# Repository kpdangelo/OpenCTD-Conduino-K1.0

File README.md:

# OpenCTD-Conduino-K1.0
OpenCTD with a Conduino inspired K1.0 graphite conductivity sensor

________________________________________
This CTD sensor started with the Open CTD plan. It evolved with the ideas from the UCSB researchers' Conduino repurposed-micro-USB probe. I was not able to solve the drift and consistency issues with the USB probe, so I have connected an Atlas Scientific K1.0 conductivity probe using the Conduino/AD5933 network analyzer based system. The benefit of using the AD5933 based system is that a calibration is required to convert the probe reading to Conductivity, providing a teaching opportunity on instrumentation. 
________________________________________

This project merges the Oceanography for Everyone Open CTD with the Conduino conductivity sensor, and an Atlas Scientific graphite probe.

Open CTD: https://github.com/OceanographyforEveryone/OpenCTD

Conduino: Marco Carminati, Paolo Luzzatto-Fegiz, Conduino: Affordable and high-resolution multichannel water conductivity sensor using micro USB connectors, In Sensors and Actuators B: Chemical, Volume 251, 2017, Pages 1034-1041, ISSN 0925-4005, https://doi.org/10.1016/j.snb.2017.05.184.

Follow the basic assembly instructions from OpenCTD along with the included instructions for constructing a Conduino.

PCBs can be ordered from OSHPARK, or Eagle and Gerber files are included here. Most of the assembly is with surface mount 0603 components. Doable without a stencil, solder paste and reflow, but easier with.

The system goes into a 2" PVC pipe and seals with Marine Epoxy and a 3D printed plug (file included here). See “Conduino K1.0 Pipe Assembly.pdf” file.

The Conduino PCB contains an analog mux that is not necessary when used with the K1.0 probe. To omit the mux, solder in 0 Ohm resistors R6 and R8 and leave U6 out. The mux was an attempt to zero out the drift seen when using the USB based probe. It didn’t work, but is left in for future experimentation.

The whole thing can be put together for around $300.

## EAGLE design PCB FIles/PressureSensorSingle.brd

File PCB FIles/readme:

These are the PCB files generated using Autodesk's Eagle CAD package.
*.sch and *.brd - Eagle Files
*.zip - gerbers
pdf's of the schematics too.

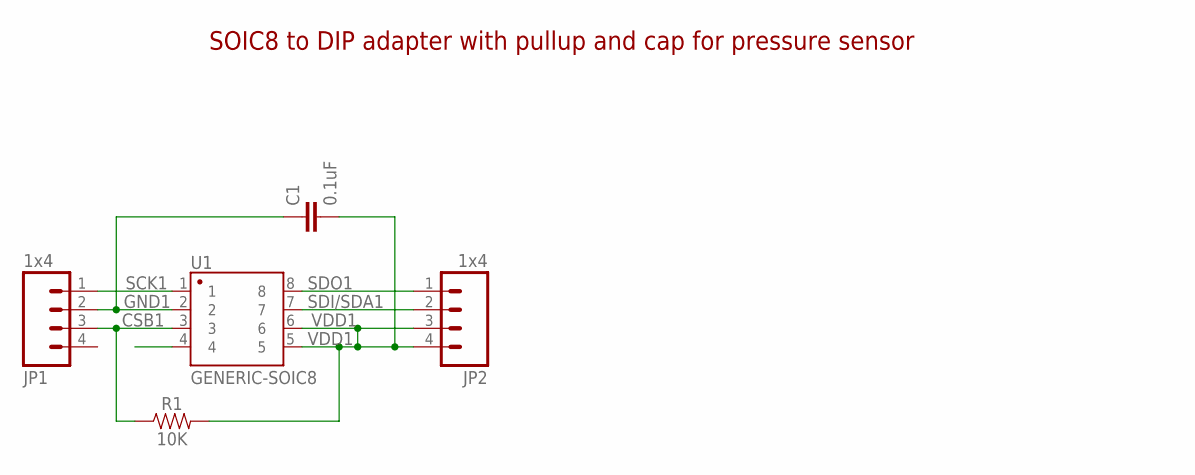
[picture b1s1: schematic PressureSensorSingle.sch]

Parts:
C1: 0.1uF; 0603
JP1: 1x4; 1X04_NO_SILK
JP2: 1x4; 1X04_NO_SILK_ALL_ROUND
R1: 10K; 0603
U1: GENERIC-SOIC8; SO08-UNIVERSAL

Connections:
CSB1: JP1.3, R1.1, U1.3
GND1: C1.1, JP1.2, U1.2
NC1: U1.4
SCK1: JP1.1, U1.1
SDI/SDA1: JP2.2, U1.7
SDO1: JP2.1, U1.8
VDD1: C1.2, JP2.3, JP2.4, R1.2, U1.5, U1.6

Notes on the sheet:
SOIC8 to DIP adapter with pullup and cap for pressure sensor

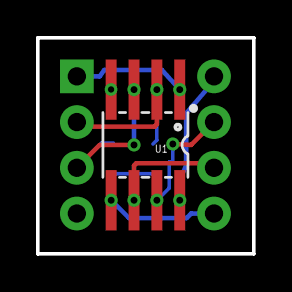
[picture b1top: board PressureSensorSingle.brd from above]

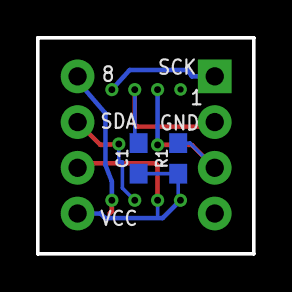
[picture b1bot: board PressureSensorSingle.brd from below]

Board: 2 copper layers, 12.0 x 12.0 mm, 5 parts (2 on the bottom side), 6 nets.

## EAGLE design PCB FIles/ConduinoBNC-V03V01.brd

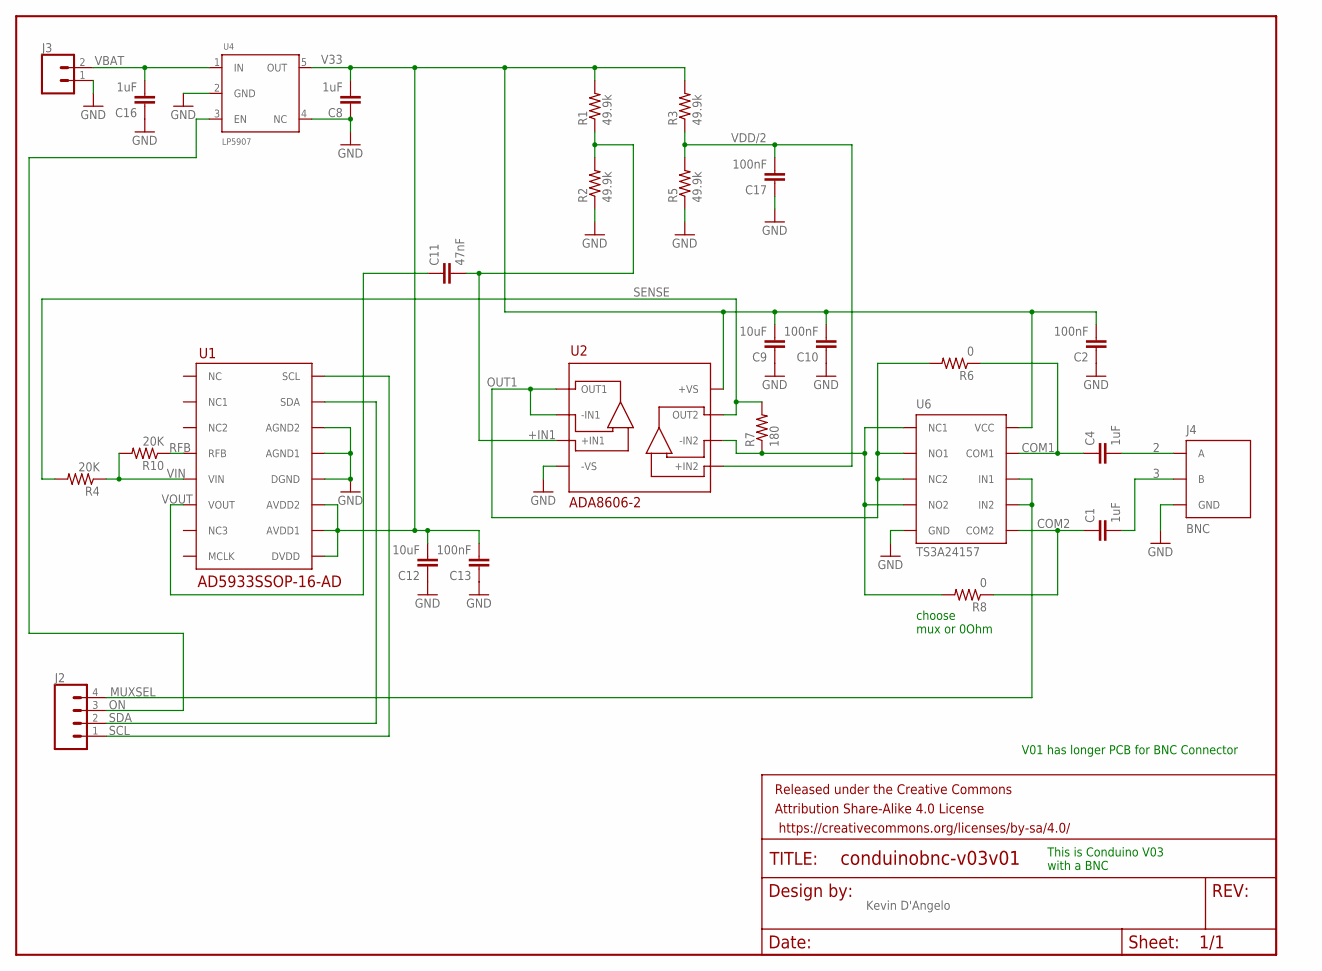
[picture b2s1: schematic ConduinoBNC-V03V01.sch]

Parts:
C1, C4, C8, C16: 1uF; 0603-CAP
C2, C10, C13, C17: 100nF; 0603-CAP
C9, C12: 10uF; 0603-CAP
C11: 47nF; 0603-CAP
FRAME1: FRAME-LETTER; CREATIVE_COMMONS
J2: CONN_041X04_NO_SILK; 1X04_NO_SILK
J3: CONN_021X02_NO_SILK; 1X02_NO_SILK
J4: BNC
R1, R2, R3, R5: 49.9k; 0603-RES
R4, R10: 20K; 0603-RES
R6, R8: 0; 0603-RES
R7: 180; 0603-RES
U1: AD5933SSOP-16-AD; SSOP-16-AD
U2: ADA8606-2; SOIC_N
U4: LP5907; SOT23-5L
U6: TS3A24157; VSSOP-10

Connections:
2: C4.2, J4.P$1 (A)
3: C1.2, J4.P$2 (B)
+IN1: C11.2, R1.1, R2.2, U2.P$3 (+IN1)
-IN2: R7.1, R8.2, U2.P$6 (-IN2), U6.P$1 (NC1), U6.P$4 (NO2)
COM1: C4.1, R6.1, U6.P$9 (COM1)
COM2: C1.1, R8.1, U6.P$6 (COM2)
GND: C2.1, C8.1, C9.1, C10.1, C12.1, C13.1, C16.1, C17.1, J3.1, J4.P$3 (GND), J4.P$4 (GND), R2.1, R5.1, U1.P$12 (DGND), U1.P$13 (AGND1), U1.P$14 (AGND2), U2.P$4 (-VS), U4.2 (GND), U4.4 (NC), U6.P$5 (GND)
MUXSEL: J2.4, U6.P$7 (IN2), U6.P$8 (IN1)
ON: J2.3, U4.3 (EN)
OUT1: R6.2, U2.P$1 (OUT1), U2.P$2 (-IN1), U6.P$2 (NO1), U6.P$3 (NC2)
RFB: R10.1, U1.P$4 (RFB)
SCL: J2.1, U1.P$16 (SCL)
SDA: J2.2, U1.P$15 (SDA)
SENSE: R4.2, R7.2, U2.P$7 (OUT2)
V33: C2.2, C8.2, C9.2, C10.2, C12.2, C13.2, R1.2, R3.2, U1.P$9 (DVDD), U1.P$10 (AVDD1), U1.P$11 (AVDD2), U2.P$8 (+VS), U4.5 (OUT), U6.P$10 (VCC)
VBAT: C16.2, J3.2, U4.1 (IN)
VDD/2: C17.2, R3.1, R5.2, U2.P$5 (+IN2)
VIN: R4.1, R10.2, U1.P$5 (VIN)
VOUT: C11.1, U1.P$6 (VOUT)

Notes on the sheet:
choose mux or 0Ohm
This is Conduino V03 with a BNC
Kevin D'Angelo
V01 has longer PCB for BNC Connector

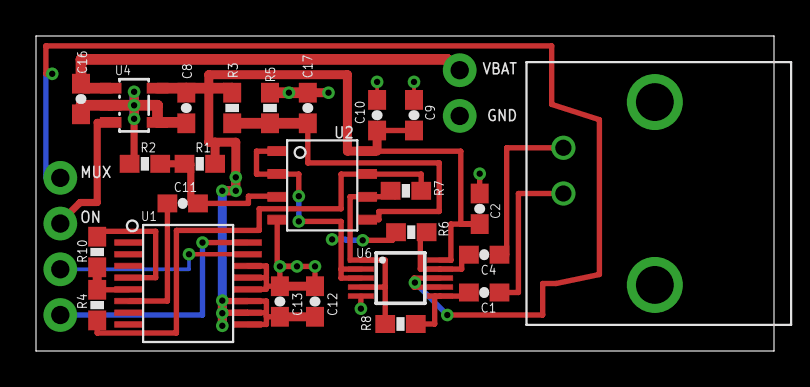
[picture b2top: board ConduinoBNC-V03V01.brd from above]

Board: 2 copper layers, 41.0 x 17.5 mm, 28 parts (0 on the bottom side), 19 nets.

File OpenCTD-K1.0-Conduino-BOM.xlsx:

Part | Device | Package | Description
Conduino V03
C1,C4,C8,C16 | 1uF | 0603-CAP | Capacitor | 0.15 | 0.6 | https://www.digikey.com/product-detail/en/tdk-corporation/CG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
C2,C10,C13,C17 | 100nF | 0603-CAP | Capacitor | 0.1 | 0.4 | https://www.digikey.com/product-detail/en/samsung-electro-me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
C9,C12 | 10uF | 0603-CAP | Capacitor | 0.36 | 0.72 | https://www.digikey.com/product-detail/en/samsung-electro-me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
C11 | 47nF | 0603-CAP | Capacitor | 0.22 | 0.22 | https://www.digikey.com/product-detail/en/kemet/C0603C473J4R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
J4 | BNC | BNC |  | 1.62 | 1.62 | https://www.digikey.com/product-detail/en/te-connectivity-am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
R1,R2,R3,R5 | 49.9k | 0603-RES | Resistor | 0.35 | 1.4 | https://www.digikey.com/product-detail/en/panasonic-electron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
R4,R10 | 20K | 0603-RES | Resistor | 0.19 | 0.38 | https://www.digikey.com/product-detail/en/yageo/RT0603DRD072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
R6,R8 | 0 | 0603-RES | Resistor | 0.1 | 0.2 | https://www.digikey.com/product-detail/en/panasonic-electron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
R7 | 180 | 0603-RES | Resistor | 0.35 | 0.35 | https://www.digikey.com/product-detail/en/panasonic-electron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
U1 | AD5933SSOP-16-AD | SSOP-16-AD |  | 35.96 | 35.96 | https://www.digikey.com/product-detail/en/analog-devices-inc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
U2 | ADA8606-2 | SOIC_N |  | 3.71 | 3.71 | https://www.digikey.com/product-detail/en/analog-devices-inc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
U4 | LP5907 | SOT23-5L |  | 0.65 | 0.65 | https://www.digikey.com/product-detail/en/texas-instruments/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
U6 | TS3A24157 | VSSOP-10 |  | 1.05 | 1.05 | https://www.digikey.com/product-detail/en/texas-instruments/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
PCB |  |  |  | 1.85 | 1.85 | https://www.oshpark.com/shared_projects/RJHBt9SN
OpenCTD-V04
R1 | 4.7K | AXIAL-0.4 | Resistor
U1 | QDUINO_MINI | QDUINO_MINI |  | 29.95 | 29.95 | https://www.sparkfun.com/products/13614
U2 | CONDUINO-V03 | CONDUINO_V03 |  |  |  | See above
U3 | SD-CARD-READER-MICRO-INOUT | SD-CARD-READER-105162 |  | 1.08 | 1.08 | https://www.digikey.com/product-detail/en/molex-llc/10516200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
 | Headers for Qduino |  |  | 0.81 | 0.81 | https://www.digikey.com/product-detail/en/sullins-connector-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
PCB |  |  |  | 8.26 | 8.26 | https://www.oshpark.com/shared_projects/qzoyn3Dc
Pressure Sensor Single PCB
C1 | 0.1uF | 0603-CAP | Capacitor | 0.1 | 0.1 | https://www.digikey.com/product-detail/en/samsung-electro-me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
R1 | 10K | 0603-RES | Resistor | 0.18 | 0.18 | https://www.digikey.com/product-detail/en/panasonic-electron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
 | Pressure Sensor | MS580314BA01-00 |  | 13.82 | 13.82 | https://www.digikey.com/product-detail/en/sullins-connector-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
PCB |  |  |  | 0.38 | 0.38 | https://www.oshpark.com/shared_projects/K8ReguM0
Conductivity Sensor
K-1.0 | Atlas Scientific |  |  | 139 | 139 | https://www.atlas-scientific.com/product_pages/probes/ec_k1-0.html
Temperature Sensor
 | Gikfun DS18B20 |  |  | 8.98 | 8.98 | https://www.amazon.com/gp/product/B00Q9YBIJI/ref=oh_aui_deta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
 | 2" Gripper |  |  | 9.39 | 9.39 | https://www.amazon.com/gp/product/B000VYNUAW/ref=oh_aui_deta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
 | 2 AH Li-Ion Battery |  |  | 12.5 | 12.5 | https://www.adafruit.com/product/2011
 |  |  |  | Total: | 273.56
Note: PCBs are ordered 3 at a time from OshPark, the single PCB price is shown 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
Note: when ordering the batteries from Adafruit, you have to order something el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
 |  |  |  |  | 0

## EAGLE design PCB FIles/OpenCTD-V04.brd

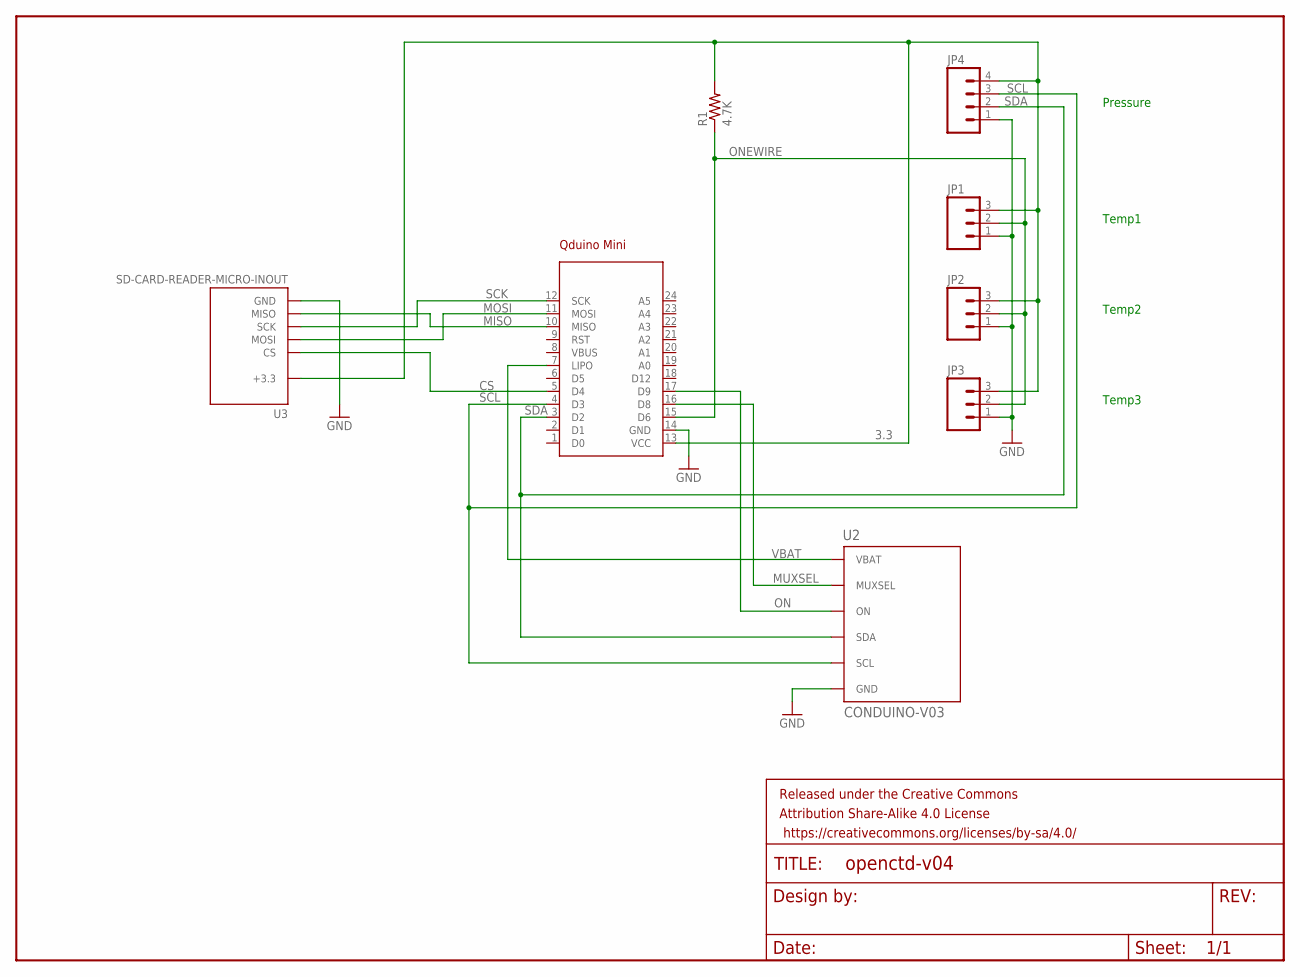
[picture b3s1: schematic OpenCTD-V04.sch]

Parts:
FRAME1: FRAME-LETTER; CREATIVE_COMMONS
JP1, JP2, JP3: M031X03_NO_SILK; 1X03_NO_SILK
JP4: M041X04_NO_SILK; 1X04_NO_SILK
R1: 4.7K; AXIAL-0.4
U1: QDUINO_MINI
U2: CONDUINO-V03; CONDUINO_V03
U3: SD-CARD-READER-MICRO-INOUT; SD-CARD-READER-105162

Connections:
3.3: JP1.3, JP2.3, JP3.3, JP4.4, R1.P$2 (2), U1.13 (VCC), U3.P$4 (+3.3)
CS: U1.5 (D4), U3.P$2 (CS)
GND: JP1.1, JP2.1, JP3.1, JP4.1, U1.14 (GND), U2.5 (GND), U3.G1 (GND), U3.G2 (GND), U3.G3 (GND), U3.G4 (GND), U3.P$6 (GND)
MISO: U1.10 (MISO), U3.P$7 (MISO)
MOSI: U1.11 (MOSI), U3.P$3 (MOSI)
MUXSEL: U1.16 (D8), U2.4 (MUXSEL)
ON: U1.17 (D9), U2.3 (ON)
ONEWIRE: JP1.2, JP2.2, JP3.2, R1.P$1 (1), U1.15 (D6)
SCK: U1.12 (SCK), U3.P$5 (SCK)
SCL: JP4.3, U1.4 (D3), U2.1 (SCL)
SDA: JP4.2, U1.3 (D2), U2.2 (SDA)
VBAT: U1.7 (LIPO), U2.6 (VBAT)

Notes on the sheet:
Pressure
Temp1
Temp2
Temp3

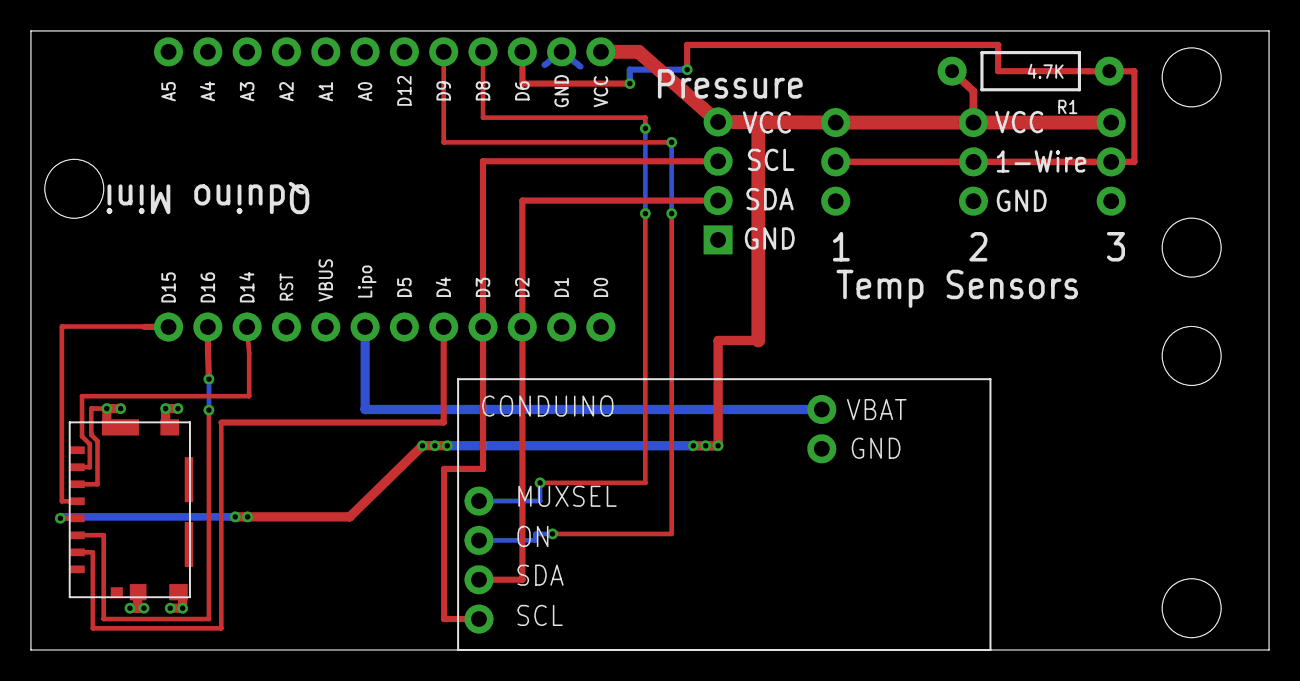
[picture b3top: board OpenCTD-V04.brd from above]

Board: 2 copper layers, 80.0 x 40.0 mm, 9 parts (0 on the bottom side), 12 nets.

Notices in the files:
parts and their libraries:
SparkFun-Aesthetics: Licensing: Creative Commons ShareAlike 4.0 International - https://creativecommons.org/licenses/by-sa/4.0
SparkFun-Aesthetics: Released under the Creative Commons
SparkFun-Aesthetics: https://creativecommons.org/licenses/by-sa/4.0
